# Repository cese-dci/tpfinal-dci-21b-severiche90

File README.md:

## Trabajo práctico final de la asignatura DCI ##
Este repositorio contiene el trabajo práctico final para la asignatura de Diseño de Circuitos Impresos de la carrera de posgrado de FIUBA.

* Autor: Severiche Jose
* Título corto del trabajo: Conversor DC-DC Step Up CN6009
* Descripción: el CN6009 es un regulador-elevador de voltaje ajustable, basado su funcionamiento en fuentes conmutadas, tambien denominado BOOST. Para la generacion y control del voltaje de salida este modulo utiliza el integrado XL6009E1, que se caracteriza por generar pulsos de pwm a altas frecuencias.
 * caracteristicas:
   * voltaje de entrada:5V-32V
   * voltaje de salida:5V-35V ajustable
   * Corriente maxima de entrada:4A
   * Corriente maxima de salida:3A
   * Frecuencia de operacion:400KHz
   * Eficiencia aproximada:94%
   * Temperatura de operacion: de -40 a 85 ºC
  
## Licencia de este trabajo ##
CERN Open Hardware License (OHL)
Ver la sección "What license should I use?": https://www.oshwa.org/faq/

## Estructura del TP FINAL ##

Se propone y se pide utilizar la siguiente estructura.

* doc: Toda la información sobre el circuito, principalmente de autoría o procesamiento propio. Por ejemplo:
  * Notas de ingeniería propias.
  * Notas de aplicación propias.
  * Estudios previos, estado del arte, resumen de las investigaciones.
  * Notas con cálculos.
  * Dibujos adicionales.
  * Fotos de los prototipos.
  * Presupuestos, cotizaciones.
* info: Toda la iformación recolectada, principalmente de terceros, como por ejemplo:
  * Hojas de datos.
  * Notas de aplicación.
  * Info de productos comerciales.
  * Info en internet.
* pcb: Archivos de diseño esquemático y pcb.

Dependiendo la magnitud del proyecto, tendremos más o menos información en estos directorios. 
Revisar los README.md en cada directorio para conocer las pautas de cada uno para este TP.

NOTA: El alumno puede y debe borrar de este archivo todo lo que considere necesario, por ejemplo las aclaraciones del docente y esta misma nota.

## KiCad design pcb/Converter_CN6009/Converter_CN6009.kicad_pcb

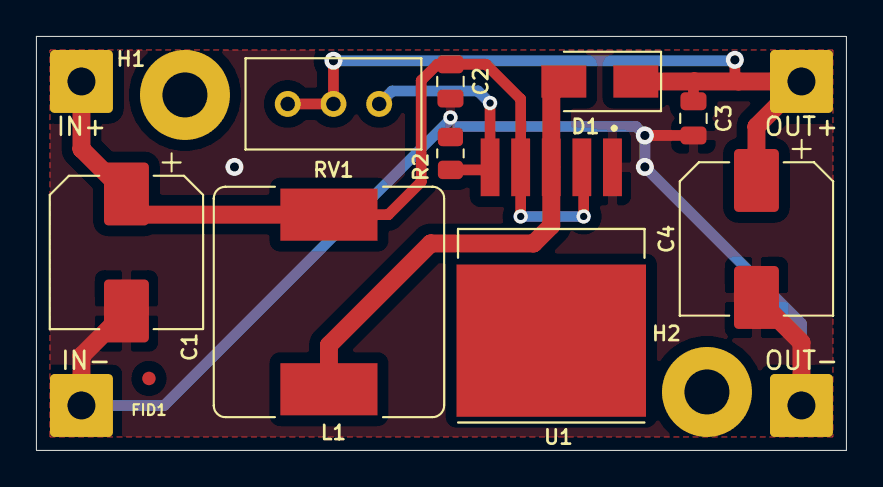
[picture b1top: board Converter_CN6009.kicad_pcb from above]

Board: 2 copper layers, 45.0 x 23.0 mm, 16 parts (0 on the bottom side), 5 nets.

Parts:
C1: 220uF; CP_Elec_8x10
C2, C3: 1uF; C_0805_2012Metric
C4: 100uF; CP_Elec_8x10
D1: SS34; D_SMA
FID1: Fiducial; Fiducial_0.75mm_Mask1.5mm
H1, H2: MountingHole; MountingHole_2.5mm_Pad
IN+: J1; SolderWire-0.75sqmm_1x01_D1.25mm_OD3.5mm
IN-: J2; SolderWire-0.75sqmm_1x01_D1.25mm_OD3.5mm
L1: 470uH; L_Bourns_SRR1260
OUT+: J3; SolderWire-0.75sqmm_1x01_D1.25mm_OD3.5mm
OUT-: J4; SolderWire-0.75sqmm_1x01_D1.25mm_OD3.5mm
R2: 1.3K; R_0805_2012Metric
RV1: 50K; Potentiometer_Bourns_3296W_Vertical
U1: XL6009; DPAK170P1435X465-6N

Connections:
GND: C1.2, C2.2, C3.2, C4.2, IN-.1, OUT-.1, R2.2, U1.1
unnamed: C1.1, C2.1, IN+.1, L1.1, U1.2, U1.4
unnamed: C3.1, C4.1, D1.1, OUT+.1, RV1.1, RV1.2
unnamed: D1.2, L1.2, U1.3
unnamed: R2.1, RV1.3, U1.5

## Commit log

2021-08-07 se agrego documentos en la carpeta doc y info
2021-08-07 cambio en readme
2021-08-15 se agrego esquematico, huellas y modelos3d
2021-08-16 se agrego borde, agujero y posicionamiento
2021-08-24 se realizo ruteo de pcb y correciones
2021-09-03 se realizo todas las correcciones para la revision final
2021-09-04 ultima correccion para revision final

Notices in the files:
pcb/Converter_CN6009/Converter_CN6009.kicad_pcb:
License : CERN Open Hardware License (OHL)
